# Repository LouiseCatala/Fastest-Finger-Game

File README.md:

<div align="center">

**KICAD · PCB LAYOUT · PRELIMINARY SCHEMATIC**

# FASTEST FINGER

### A three-player game concept, explored through PCB design.

[Explore the project](#project-overview) · [Documentation](#project-documentation) · [Contact the developer](mailto:louise.catala24@gmail.com)

</div>

<p align="center"><em>Existing KiCad 3D visualization. Component models are approximate; this is not a photograph of a fabricated board.</em></p>

## Project overview

An editable PCB-layout study for a three-player Fastest Finger game concept. The board brings player controls, a display, and supporting components into one visual design that can be explored in KiCad.

| At a glance | What it means |
| --- | --- |
| **3 players** | Three-player control layout |
| **KiCad project** | Editable board and schematic files |
| **174 × 128 mm** | Documented nominal board dimensions |

## Explore the design, with its status in view

**Design status: preliminary, not manufacturing-ready.** The layout was reconstructed from a supplied reference image. Traces are not fully routed, electrical connections and component choices need verification, and FPGA code is not included. The value here is an inspectable layout and schematic study, with its limitations stated openly.

*Preliminary schematic preview; retain the verification requirements in the original documentation below.*

[Explore the project package](Fastest-Finger-RevB)

## Project documentation

<details>
<summary><strong>Open the original project notes, files, and setup instructions</strong></summary>

# FASTEST FINGER — Made by Catala

This is an **editable KiCad PCB Editor board layout** recreated from the supplied reference image.

**Changes from the reference**
- All six names across the top have been removed.
- The bottom-center text now reads **Made by Catala**.
- The original title, three-player layout, approximate placement, and white decorative graphics are retained.

## PCB 3D Preview

The 3D visualization of the Fastest Finger PCB design created using KiCad.

## Schematic Diagram

The preliminary schematic diagram of the Fastest Finger circuit designed using KiCad Schematic Editor.

## Open in KiCad

1. Extract the whole ZIP; keep the `models` folder with the project files.
2. In KiCad Project Manager choose **File → Open Project** and select `Fastest_Finger_Made_by_Catala.kicad_pro`.
3. Double-click `Fastest_Finger_Made_by_Catala.kicad_pcb` from the project tree, or choose the PCB Editor shortcut.
4. In PCB Editor, use **View → 3D Viewer** (`Alt+3` on many systems) to see the approximate component models.
5. Edit text and locations directly on the **F.SilkS** and other PCB layers.
6. Open **Schematic Editor** to view or modify the `.kicad_sch` file.

Alternatively, start standalone PCB Editor and use **File → Open** to select the `.kicad_pcb` file. Do not try to select `.kicad_pcb` from KiCad Project Manager's **Open Project** file dialog, which filters for `.kicad_pro`.

## Hardware Components

| Component | Quantity |
|-----------|----------|
| Tang Nano 9K FPGA Board | 1 |
| 4-Digit 7-Segment Display | 1 |
| Player Push Buttons | 3 |
| START Button | 1 |
| RESET Button | 1 |
| NPN Transistors | 5 |
| Resistors | 17 |
| Capacitors | 2 |
| Diodes | 4 |
| LEDs | 2 |
| Buzzer | 1 |
| Mounting Holes | 4 |
| Printed Circuit Board | 1 |

## Important Limitation

This is a **visual/layout reconstruction with a preliminary schematic, not a verified, manufacturing-ready electronic design**.

The electrical connections, FPGA pin assignments, component values, and control wiring require verification. PCB traces are not fully routed, and FPGA code is not included.

Do not send the PCB for fabrication or assume functionality without verifying the actual circuit.

Real footprints and dimensions must be checked against the specific parts to be installed, especially the four-digit display, buttons, buzzer, and diodes. Visual models are approximations, not manufacturer STEP models.

- Board nominal dimensions: **174 mm × 128 mm**.
- Tang Nano 9K: represented by a **2 × 24 pin, 2.54 mm pitch** carrier footprint.
- Editable silkscreen labels and PCB features are part of the `.kicad_pcb` file.

---

**Made by Catala**

</details>

---

## License and Support

Copyright © 2026 Orland Louise Catala. All rights reserved for my original work, except where an existing license states otherwise. Third-party materials remain subject to their respective licenses.

Please do not copy, modify, redistribute, sell, or claim my original project files as your own without my permission.

I’m a student developer with limited financial resources, and these projects represent many hours of effort. Please respect and support my work. If you would like a copy of the project files, contact me at **[louise.catala24@gmail.com](mailto:louise.catala24@gmail.com)** to discuss a cheap price. Your support helps me continue studying and creating.

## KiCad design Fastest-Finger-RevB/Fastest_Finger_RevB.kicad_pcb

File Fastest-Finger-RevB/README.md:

# FASTEST FINGER — Made by Catala

This is an **editable KiCad PCB Editor board layout** recreated from the supplied reference image.

**Changes from the reference**
- All six names across the top have been removed.
- The bottom-center text now reads **Made by Catala**.
- The original title, three-player layout, approximate placement, and white decorative graphics are retained.

## PCB 3D Preview

The 3D visualization of the Fastest Finger PCB design created using KiCad.

## Schematic Diagram

The preliminary schematic diagram of the Fastest Finger circuit designed using KiCad Schematic Editor.

## Open in KiCad

1. Extract the whole ZIP; keep the `models` folder with the project files.
2. In KiCad Project Manager choose **File → Open Project** and select `Fastest_Finger_Made_by_Catala.kicad_pro`.
3. Double-click `Fastest_Finger_Made_by_Catala.kicad_pcb` from the project tree, or choose the PCB Editor shortcut.
4. In PCB Editor, use **View → 3D Viewer** (`Alt+3` on many systems) to see the approximate component models.
5. Edit text and locations directly on the **F.SilkS** and other PCB layers.
6. Open **Schematic Editor** to view or modify the `.kicad_sch` file.

Alternatively, start standalone PCB Editor and use **File → Open** to select the `.kicad_pcb` file. Do not try to select `.kicad_pcb` from KiCad Project Manager's **Open Project** file dialog, which filters for `.kicad_pro`.

## Hardware Components

| Component | Quantity |
|-----------|----------|
| Tang Nano 9K FPGA Board | 1 |
| 4-Digit 7-Segment Display | 1 |
| Player Push Buttons | 3 |
| START Button | 1 |
| RESET Button | 1 |
| NPN Transistors | 5 |
| Resistors | 17 |
| Capacitors | 2 |
| Diodes | 4 |
| LEDs | 2 |
| Buzzer | 1 |
| Mounting Holes | 4 |
| Printed Circuit Board | 1 |

## Important Limitation

This is a **visual/layout reconstruction with a preliminary schematic, not a verified, manufacturing-ready electronic design**.

The electrical connections, FPGA pin assignments, component values, and control wiring require verification. PCB traces are not fully routed, and FPGA code is not included.

Do not send the PCB for fabrication or assume functionality without verifying the actual circuit.

Real footprints and dimensions must be checked against the specific parts to be installed, especially the four-digit display, buttons, buzzer, and diodes. Visual models are approximations, not manufacturer STEP models.

- Board nominal dimensions: **174 mm × 128 mm**.
- Tang Nano 9K: represented by a **2 × 24 pin, 2.54 mm pitch** carrier footprint.
- Editable silkscreen labels and PCB features are part of the `.kicad_pcb` file.

---

**Made by Catala**

## License and Support

Copyright © 2026 Orland Louise Catala. All rights reserved for my original work, except where an existing license states otherwise. Third-party materials remain subject to their respective licenses.

Please do not copy, modify, redistribute, sell, or claim my original project files as your own without my permission.

I’m a student developer with limited financial resources, and these projects represent many hours of effort. Please respect and support my work. If you would like a copy of the project files, contact me at **[louise.catala24@gmail.com](mailto:louise.catala24@gmail.com)** to discuss a cheap price. Your support helps me continue studying and creating.

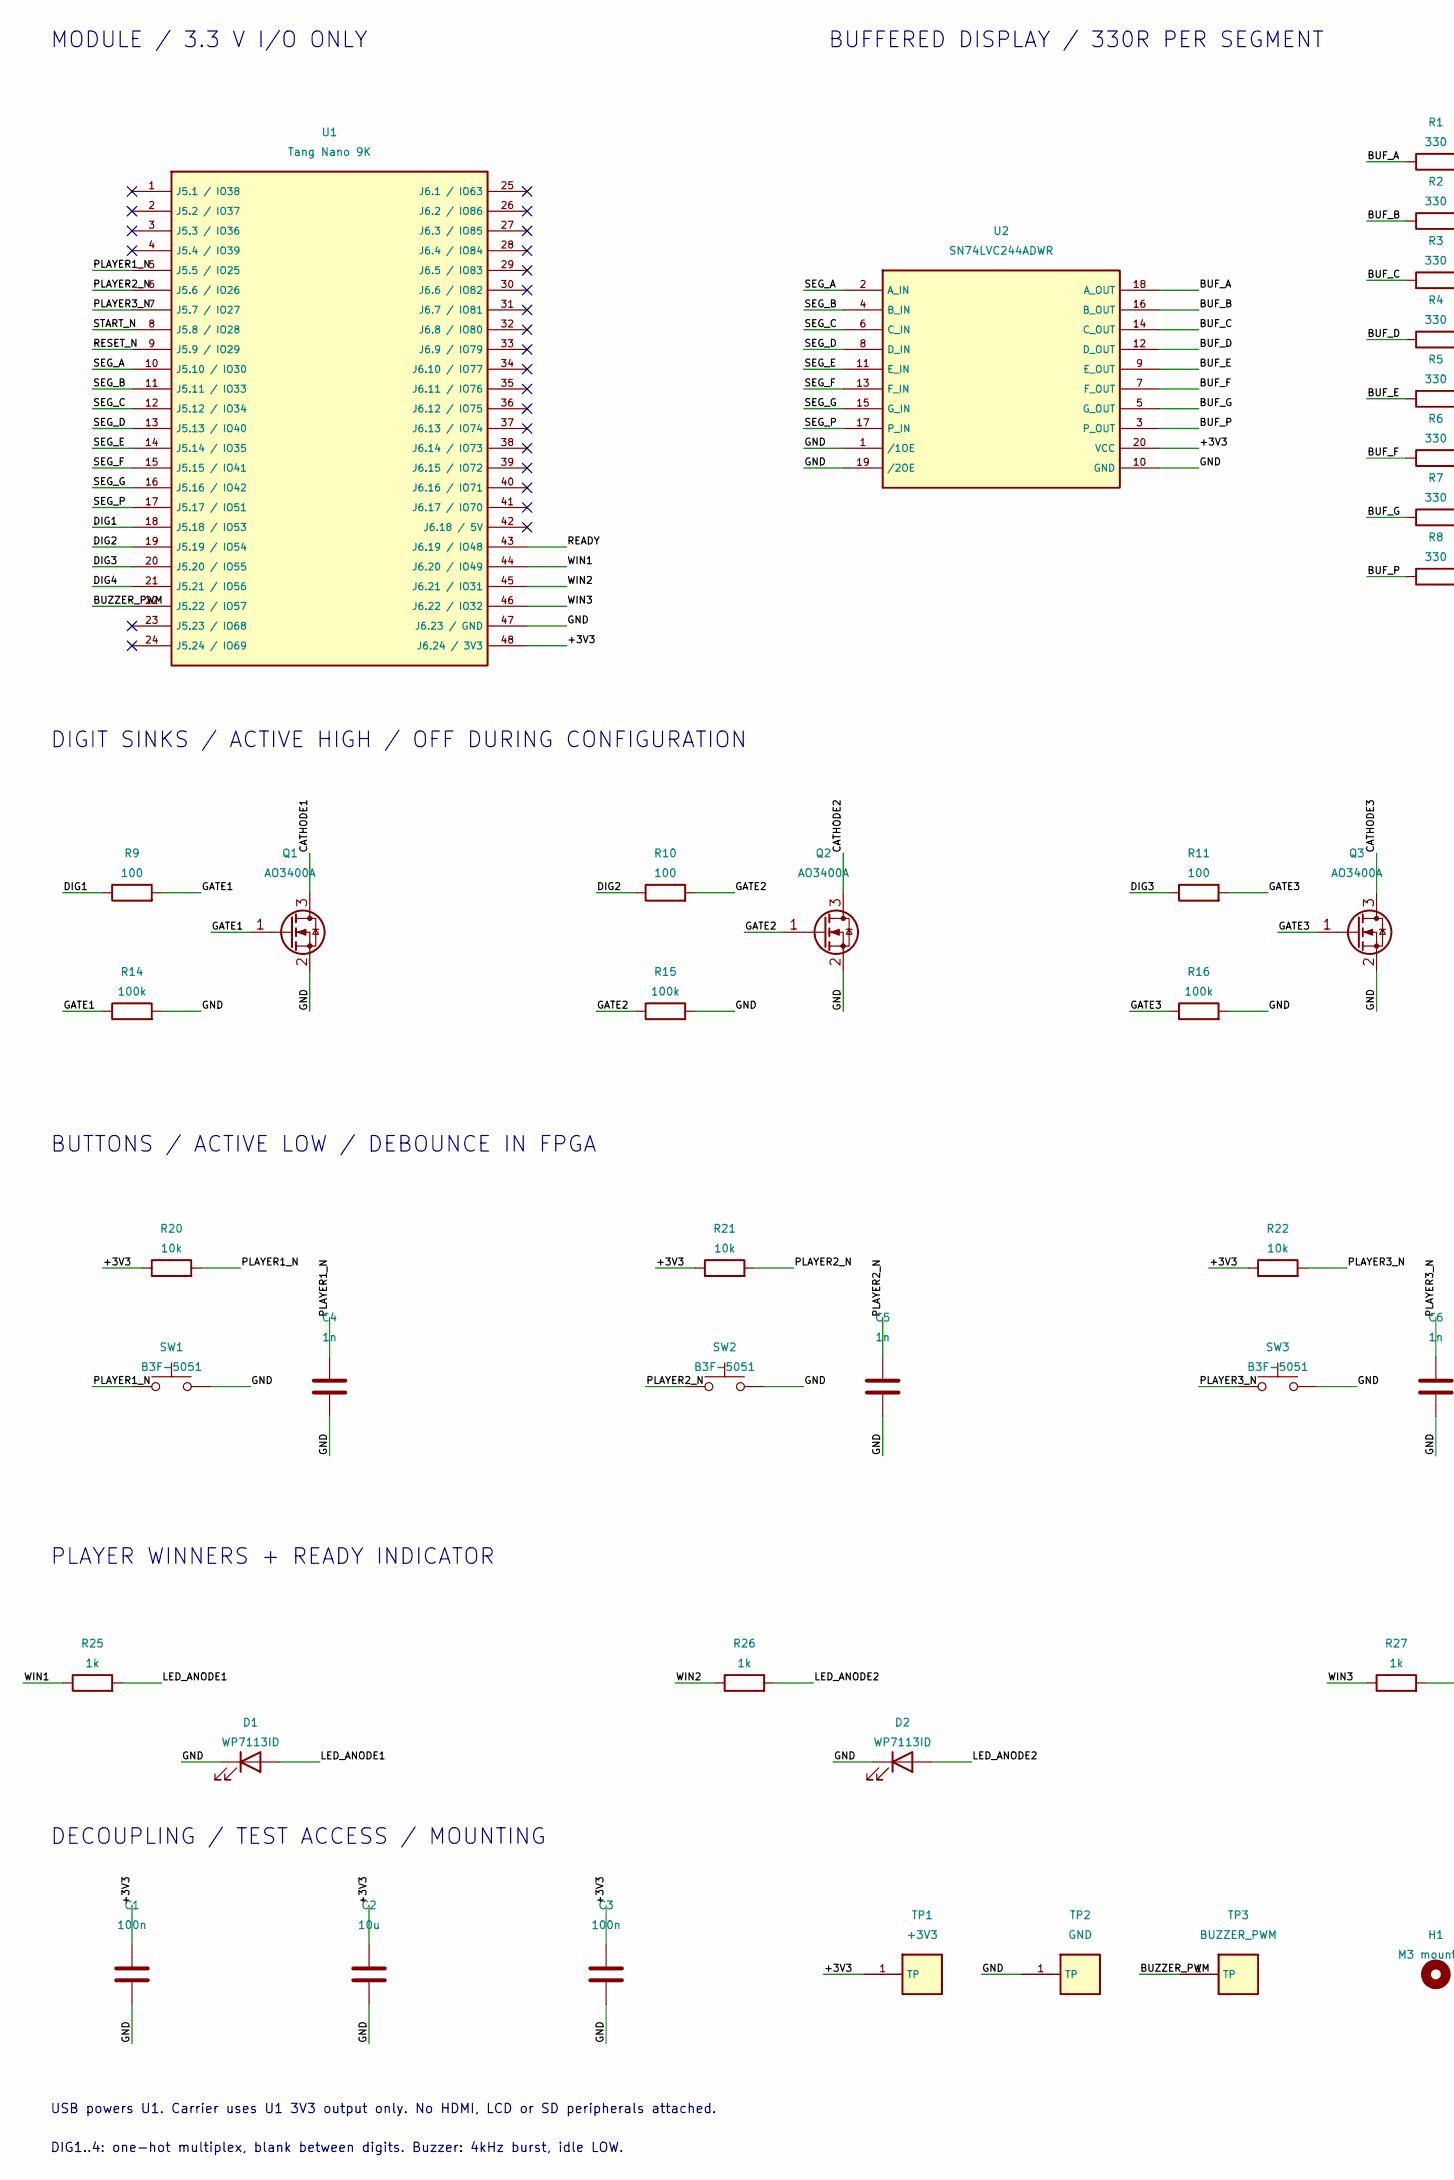
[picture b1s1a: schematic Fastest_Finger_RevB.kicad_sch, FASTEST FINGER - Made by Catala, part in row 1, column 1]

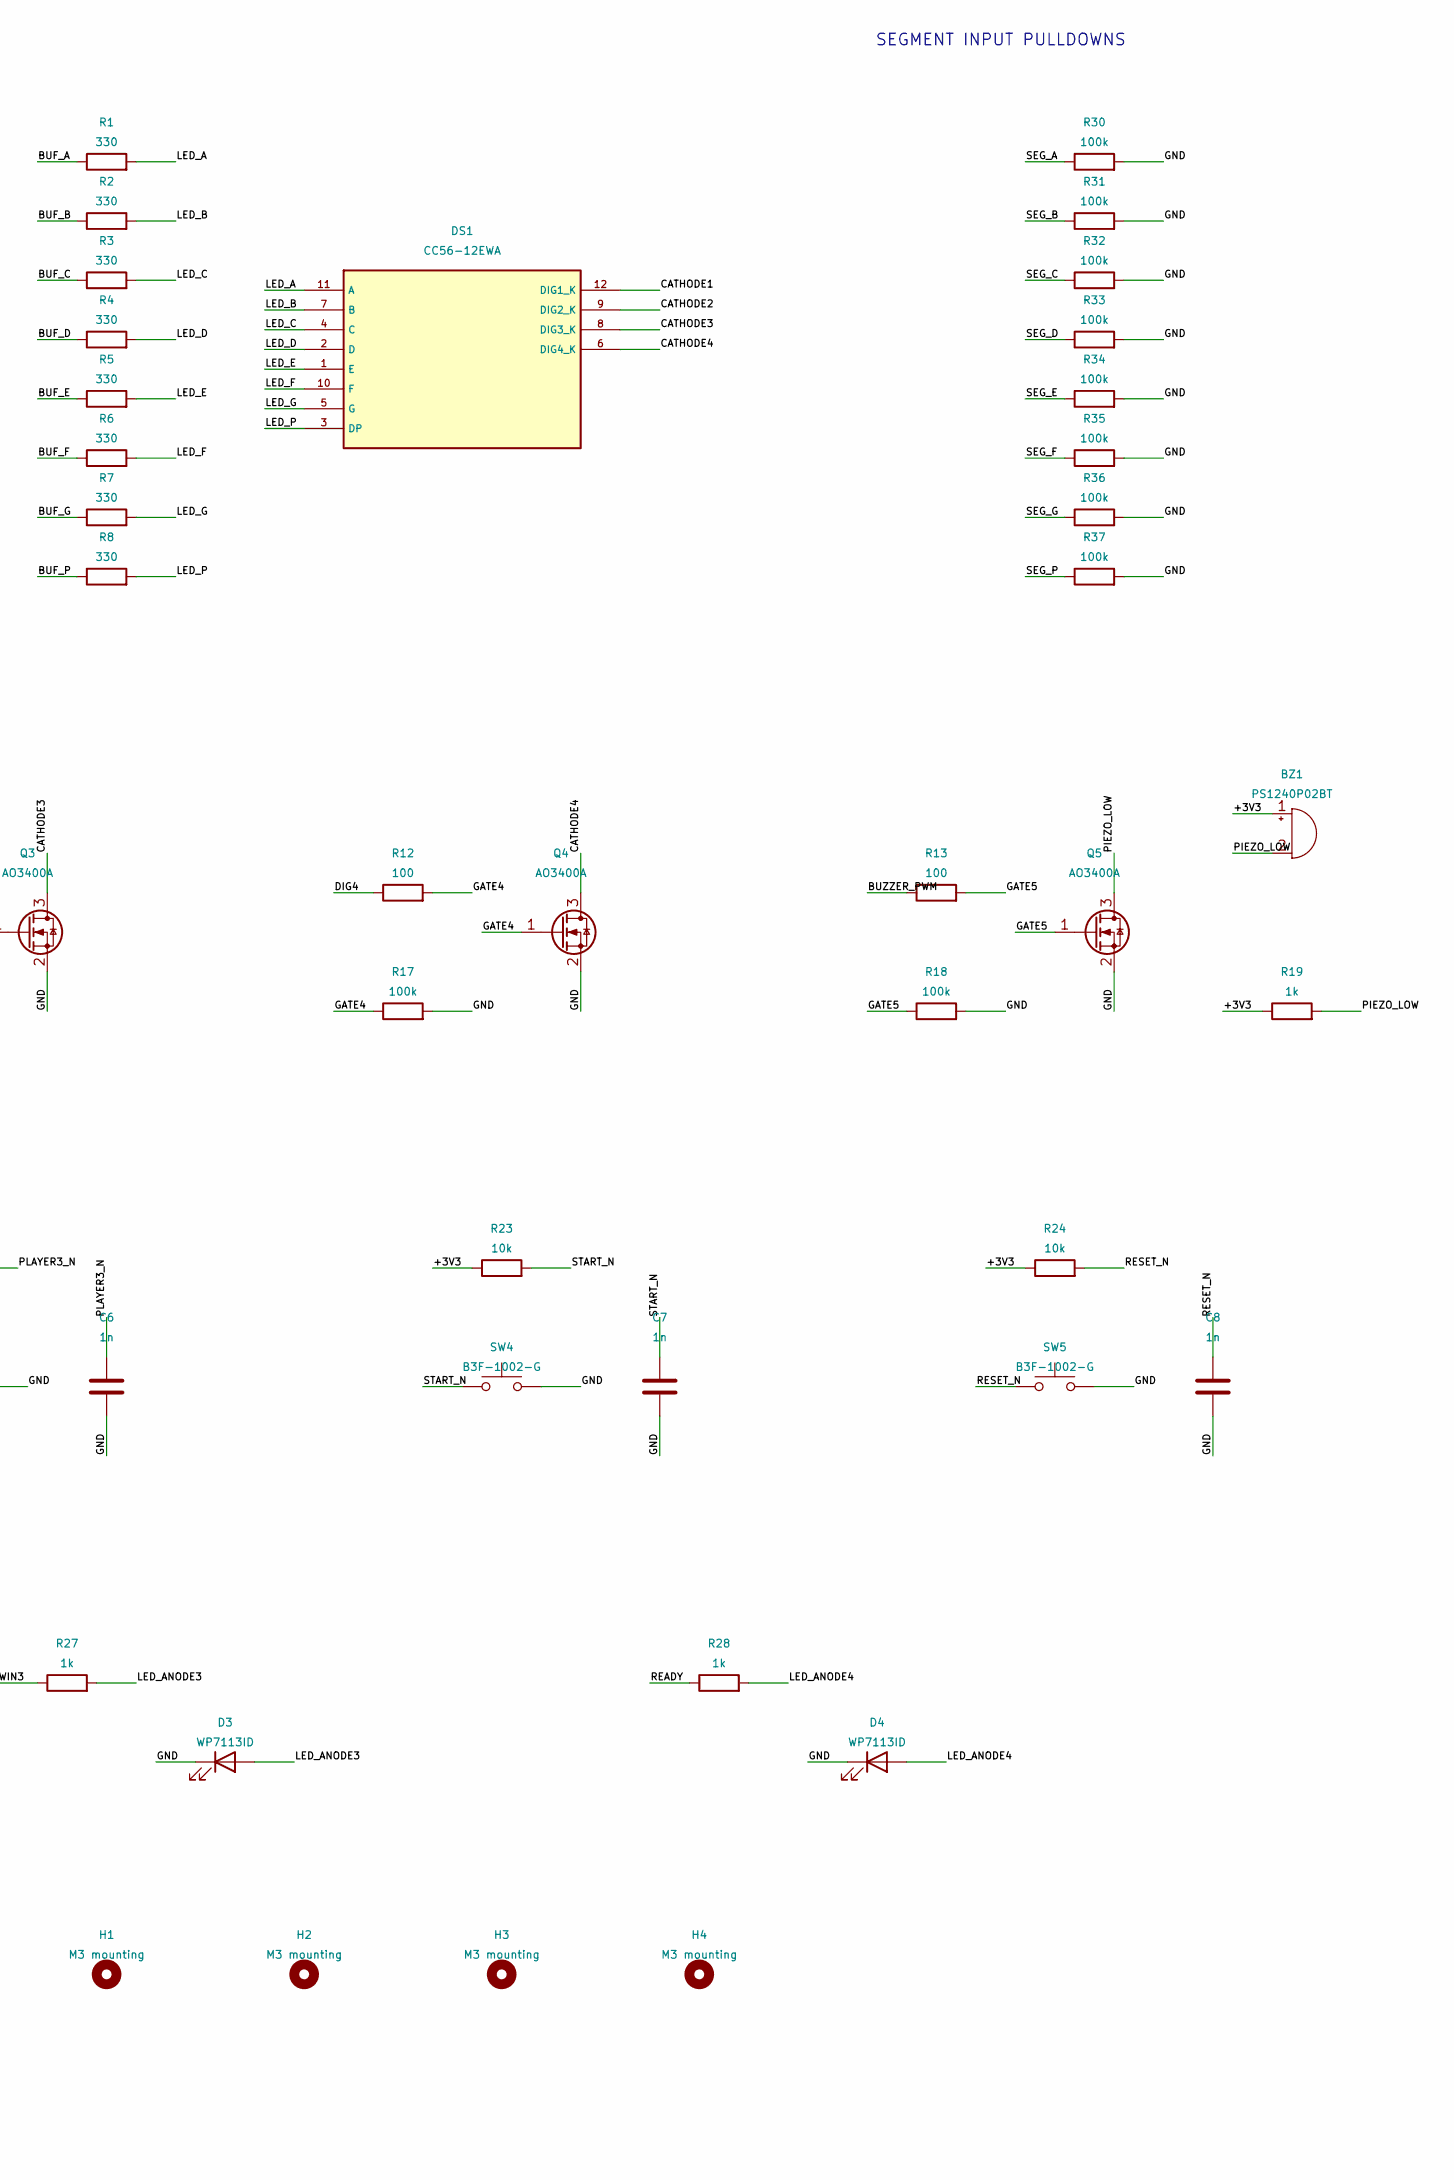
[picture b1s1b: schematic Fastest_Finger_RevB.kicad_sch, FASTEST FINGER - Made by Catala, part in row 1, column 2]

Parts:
BZ1: PS1240P02BT; Buzzer_TDK_PS1240P02BT_D12.2mm_H6.5mm; MPN PS1240P02BT
C1, C3: 100n; C_0805_2012Metric; MPN GRM21BR71H104KA01L
C2: 10u; C_0805_2012Metric; MPN GRM21BR61A106KE19L
C4, C5, C6, C7, C8: 1n; C_0805_2012Metric; MPN GRM21A5C1H102JA01D
D1, D2, D3, D4: WP7113ID; LED_D5.0mm; MPN WP7113ID
DS1: CC56-12EWA; CC56_12EWA; MPN CC56-12EWA
H1, H2, H3, H4: M3 mounting; MountingHole_3.2mm_M3; MPN M3 clearance hole
Q1, Q2, Q3, Q4, Q5: AO3400A; SOT-23; MPN AO3400A
R1, R2, R3, R4, R5, R6, R7, R8: 330; R_0805_2012Metric; MPN RC0805FR-07330RL
R9, R10, R11, R12, R13: 100; R_0805_2012Metric; MPN RC0805FR-07100RL
R14, R15, R16, R17, R18, R30, R31, R32, R33, R34, R35, R36, R37: 100k; R_0805_2012Metric; MPN RC0805FR-07100KL
R19, R25, R26, R27, R28: 1k; R_0805_2012Metric; MPN RC0805FR-071KL
R20, R21, R22, R23, R24: 10k; R_0805_2012Metric; MPN RC0805FR-0710KL
SW1, SW2, SW3: B3F-5051; SW_SPST_Omron_B3F-50xx; MPN B3F-5051
SW4, SW5: B3F-1002-G; SW_TH_Tactile_Omron_B3F-100x; MPN B3F-1002-G
TP1: +3V3; TestPoint_Pad_D2.0mm; MPN D2.0mm test pad
TP2: GND; TestPoint_Pad_D2.0mm; MPN D2.0mm test pad
TP3: BUZZER_PWM; TestPoint_Pad_D2.0mm; MPN D2.0mm test pad
U1: Tang Nano 9K; Tang_Nano_9K; MPN Tang Nano 9K
U2: SN74LVC244ADWR; SOIC-20W_7.5x12.8mm_P1.27mm; MPN SN74LVC244ADWR

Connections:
+3V3: BZ1.1 (+), C1.1, C2.1, C3.1, R19.1, R20.1, R21.1, R22.1, R23.1, R24.1, TP1.1, U1.48 (J6.24 / 3V3), U2.20 (VCC)
BUF_A: R1.1, U2.18 (A_OUT)
BUF_B: R2.1, U2.16 (B_OUT)
BUF_C: R3.1, U2.14 (C_OUT)
BUF_D: R4.1, U2.12 (D_OUT)
BUF_E: R5.1, U2.9 (E_OUT)
BUF_F: R6.1, U2.7 (F_OUT)
BUF_G: R7.1, U2.5 (G_OUT)
BUF_P: R8.1, U2.3 (P_OUT)
BUZZER_PWM: R13.1, TP3.1, U1.22 (J5.22 / IO57)
CATHODE1: DS1.12 (DIG1_K), Q1.3 (D)
CATHODE2: DS1.9 (DIG2_K), Q2.3 (D)
CATHODE3: DS1.8 (DIG3_K), Q3.3 (D)
CATHODE4: DS1.6 (DIG4_K), Q4.3 (D)
DIG1: R9.1, U1.18 (J5.18 / IO53)
DIG2: R10.1, U1.19 (J5.19 / IO54)
DIG3: R11.1, U1.20 (J5.20 / IO55)
DIG4: R12.1, U1.21 (J5.21 / IO56)
GATE1: Q1.1 (G), R9.2, R14.1
GATE2: Q2.1 (G), R10.2, R15.1
GATE3: Q3.1 (G), R11.2, R16.1
GATE4: Q4.1 (G), R12.2, R17.1
GATE5: Q5.1 (G), R13.2, R18.1
GND: C1.2, C2.2, C3.2, C4.2, C5.2, C6.2, C7.2, C8.2, D1.1 (K), D2.1 (K), D3.1 (K), D4.1 (K), Q1.2 (S), Q2.2 (S), Q3.2 (S), Q4.2 (S), Q5.2 (S), R14.2, R15.2, R16.2, R17.2, R18.2, R30.2, R31.2, R32.2, R33.2, R34.2, R35.2, R36.2, R37.2, SW1.2, SW2.2, SW3.2, SW4.2, SW5.2, TP2.1, U1.47 (J6.23 / GND), U2.1 (/1OE), U2.10 (GND), U2.19 (/2OE)
LED_A: DS1.11 (A), R1.2
LED_ANODE1: D1.2 (A), R25.2
LED_ANODE2: D2.2 (A), R26.2
LED_ANODE3: D3.2 (A), R27.2
LED_ANODE4: D4.2 (A), R28.2
LED_B: DS1.7 (B), R2.2
LED_C: DS1.4 (C), R3.2
LED_D: DS1.2 (D), R4.2
LED_E: DS1.1 (E), R5.2
LED_F: DS1.10 (F), R6.2
LED_G: DS1.5 (G), R7.2
LED_P: DS1.3 (DP), R8.2
PIEZO_LOW: BZ1.2 (-), Q5.3 (D), R19.2
PLAYER1_N: C4.1, R20.2, SW1.1, U1.5 (J5.5 / IO25)
PLAYER2_N: C5.1, R21.2, SW2.1, U1.6 (J5.6 / IO26)
PLAYER3_N: C6.1, R22.2, SW3.1, U1.7 (J5.7 / IO27)
READY: R28.1, U1.43 (J6.19 / IO48)
RESET_N: C8.1, R24.2, SW5.1, U1.9 (J5.9 / IO29)
SEG_A: R30.1, U1.10 (J5.10 / IO30), U2.2 (A_IN)
SEG_B: R31.1, U1.11 (J5.11 / IO33), U2.4 (B_IN)
SEG_C: R32.1, U1.12 (J5.12 / IO34), U2.6 (C_IN)
SEG_D: R33.1, U1.13 (J5.13 / IO40), U2.8 (D_IN)
SEG_E: R34.1, U1.14 (J5.14 / IO35), U2.11 (E_IN)
SEG_F: R35.1, U1.15 (J5.15 / IO41), U2.13 (F_IN)
SEG_G: R36.1, U1.16 (J5.16 / IO42), U2.15 (G_IN)
SEG_P: R37.1, U1.17 (J5.17 / IO51), U2.17 (P_IN)
START_N: C7.1, R23.2, SW4.1, U1.8 (J5.8 / IO28)
WIN1: R25.1, U1.44 (J6.20 / IO49)
WIN2: R26.1, U1.45 (J6.21 / IO31)
WIN3: R27.1, U1.46 (J6.22 / IO32)

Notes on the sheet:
MODULE / 3.3 V I/O ONLY
BUFFERED DISPLAY / 330R PER SEGMENT
SEGMENT INPUT PULLDOWNS
DIGIT SINKS / ACTIVE HIGH / OFF DURING CONFIGURATION
BUTTONS / ACTIVE LOW / DEBOUNCE IN FPGA
PLAYER WINNERS + READY INDICATOR
DECOUPLING / TEST ACCESS / MOUNTING
USB powers U1. Carrier uses U1 3V3 output only. No HDMI, LCD or SD peripherals attached.
DIG1..4: one-hot multiplex, blank between digits. Buzzer: 4kHz burst, idle LOW.

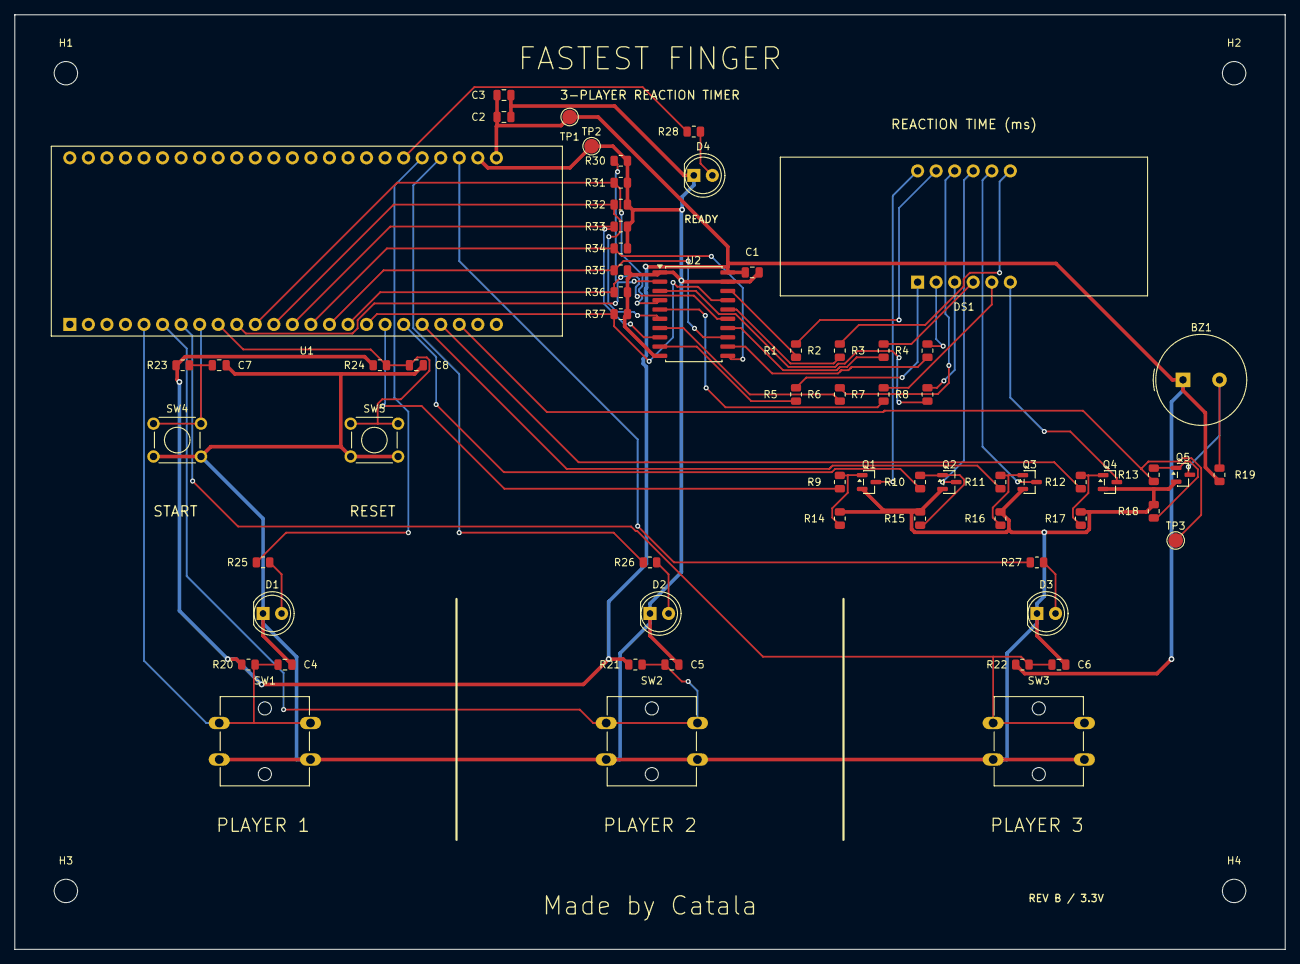
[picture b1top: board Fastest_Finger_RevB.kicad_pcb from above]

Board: 2 copper layers, 174.0 x 128.0 mm, 69 parts (0 on the bottom side), 54 nets.

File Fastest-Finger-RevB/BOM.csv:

Reference,Value,MPN,Manufacturer,Footprint,Datasheet
U1,Tang Nano 9K,Tang Nano 9K,Sipeed,FF_RevB:Tang_Nano_9K,https://dl.sipeed.com/fileList/TANG/Nano%209K/2_Schematic/Ta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
U2,SN74LVC244ADWR,SN74LVC244ADWR,Texas Instruments,FF_RevB:SOIC-20W_7.5x12.8mm_P1.27mm,https://www.ti.com/lit/ds/symlink/sn74lvc244a.pdf
DS1,CC56-12EWA,CC56-12EWA,Kingbright,FF_RevB:CC56_12EWA,https://www.kingbrightusa.com/images/catalog/SPEC/CC56-12EWA.pdf
R1,330,RC0805FR-07330RL,Yageo,FF_RevB:R_0805_2012Metric,
R30,100k,RC0805FR-07100KL,Yageo,FF_RevB:R_0805_2012Metric,
R2,330,RC0805FR-07330RL,Yageo,FF_RevB:R_0805_2012Metric,
R31,100k,RC0805FR-07100KL,Yageo,FF_RevB:R_0805_2012Metric,
R3,330,RC0805FR-07330RL,Yageo,FF_RevB:R_0805_2012Metric,
R32,100k,RC0805FR-07100KL,Yageo,FF_RevB:R_0805_2012Metric,
R4,330,RC0805FR-07330RL,Yageo,FF_RevB:R_0805_2012Metric,
R33,100k,RC0805FR-07100KL,Yageo,FF_RevB:R_0805_2012Metric,
R5,330,RC0805FR-07330RL,Yageo,FF_RevB:R_0805_2012Metric,
R34,100k,RC0805FR-07100KL,Yageo,FF_RevB:R_0805_2012Metric,
R6,330,RC0805FR-07330RL,Yageo,FF_RevB:R_0805_2012Metric,
R35,100k,RC0805FR-07100KL,Yageo,FF_RevB:R_0805_2012Metric,
R7,330,RC0805FR-07330RL,Yageo,FF_RevB:R_0805_2012Metric,
R36,100k,RC0805FR-07100KL,Yageo,FF_RevB:R_0805_2012Metric,
R8,330,RC0805FR-07330RL,Yageo,FF_RevB:R_0805_2012Metric,
R37,100k,RC0805FR-07100KL,Yageo,FF_RevB:R_0805_2012Metric,
Q1,AO3400A,AO3400A,Alpha & Omega,FF_RevB:SOT-23,https://www.aosmd.com/sites/default/files/res/datasheets/AO3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
R9,100,RC0805FR-07100RL,Yageo,FF_RevB:R_0805_2012Metric,
R14,100k,RC0805FR-07100KL,Yageo,FF_RevB:R_0805_2012Metric,
Q2,AO3400A,AO3400A,Alpha & Omega,FF_RevB:SOT-23,https://www.aosmd.com/sites/default/files/res/datasheets/AO3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
R10,100,RC0805FR-07100RL,Yageo,FF_RevB:R_0805_2012Metric,
R15,100k,RC0805FR-07100KL,Yageo,FF_RevB:R_0805_2012Metric,
Q3,AO3400A,AO3400A,Alpha & Omega,FF_RevB:SOT-23,https://www.aosmd.com/sites/default/files/res/datasheets/AO3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
R11,100,RC0805FR-07100RL,Yageo,FF_RevB:R_0805_2012Metric,
R16,100k,RC0805FR-07100KL,Yageo,FF_RevB:R_0805_2012Metric,
Q4,AO3400A,AO3400A,Alpha & Omega,FF_RevB:SOT-23,https://www.aosmd.com/sites/default/files/res/datasheets/AO3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
R12,100,RC0805FR-07100RL,Yageo,FF_RevB:R_0805_2012Metric,
R17,100k,RC0805FR-07100KL,Yageo,FF_RevB:R_0805_2012Metric,
Q5,AO3400A,AO3400A,Alpha & Omega,FF_RevB:SOT-23,https://www.aosmd.com/sites/default/files/res/datasheets/AO3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
R13,100,RC0805FR-07100RL,Yageo,FF_RevB:R_0805_2012Metric,
R18,100k,RC0805FR-07100KL,Yageo,FF_RevB:R_0805_2012Metric,
BZ1,PS1240P02BT,PS1240P02BT,TDK,FF_RevB:Buzzer_TDK_PS1240P02BT_D12.2mm_H6.5mm,https://product.tdk.com/system/files/dam/doc/product/sw_piez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
R19,1k,RC0805FR-071KL,Yageo,FF_RevB:R_0805_2012Metric,
SW1,B3F-5051,B3F-5051,Omron,FF_RevB:SW_SPST_Omron_B3F-50xx,https://components.omron.com/us-en/datasheet_pdf/A070-E1.pdf
R20,10k,RC0805FR-0710KL,Yageo,FF_RevB:R_0805_2012Metric,
C4,1n,GRM21A5C1H102JA01D,Murata,FF_RevB:C_0805_2012Metric,
SW2,B3F-5051,B3F-5051,Omron,FF_RevB:SW_SPST_Omron_B3F-50xx,https://components.omron.com/us-en/datasheet_pdf/A070-E1.pdf
R21,10k,RC0805FR-0710KL,Yageo,FF_RevB:R_0805_2012Metric,
C5,1n,GRM21A5C1H102JA01D,Murata,FF_RevB:C_0805_2012Metric,
SW3,B3F-5051,B3F-5051,Omron,FF_RevB:SW_SPST_Omron_B3F-50xx,https://components.omron.com/us-en/datasheet_pdf/A070-E1.pdf
R22,10k,RC0805FR-0710KL,Yageo,FF_RevB:R_0805_2012Metric,
C6,1n,GRM21A5C1H102JA01D,Murata,FF_RevB:C_0805_2012Metric,
SW4,B3F-1002-G,B3F-1002-G,Omron,FF_RevB:SW_TH_Tactile_Omron_B3F-100x,https://components.omron.com/us-en/datasheet_pdf/A070-E1.pdf
R23,10k,RC0805FR-0710KL,Yageo,FF_RevB:R_0805_2012Metric,
C7,1n,GRM21A5C1H102JA01D,Murata,FF_RevB:C_0805_2012Metric,
SW5,B3F-1002-G,B3F-1002-G,Omron,FF_RevB:SW_TH_Tactile_Omron_B3F-100x,https://components.omron.com/us-en/datasheet_pdf/A070-E1.pdf
R24,10k,RC0805FR-0710KL,Yageo,FF_RevB:R_0805_2012Metric,
C8,1n,GRM21A5C1H102JA01D,Murata,FF_RevB:C_0805_2012Metric,
D1,WP7113ID,WP7113ID,Kingbright,FF_RevB:LED_D5.0mm,https://www.kingbrightusa.com/images/catalog/SPEC/WP7113ID.pdf
R25,1k,RC0805FR-071KL,Yageo,FF_RevB:R_0805_2012Metric,
D2,WP7113ID,WP7113ID,Kingbright,FF_RevB:LED_D5.0mm,https://www.kingbrightusa.com/images/catalog/SPEC/WP7113ID.pdf
R26,1k,RC0805FR-071KL,Yageo,FF_RevB:R_0805_2012Metric,
D3,WP7113ID,WP7113ID,Kingbright,FF_RevB:LED_D5.0mm,https://www.kingbrightusa.com/images/catalog/SPEC/WP7113ID.pdf
R27,1k,RC0805FR-071KL,Yageo,FF_RevB:R_0805_2012Metric,
D4,WP7113ID,WP7113ID,Kingbright,FF_RevB:LED_D5.0mm,https://www.kingbrightusa.com/images/catalog/SPEC/WP7113ID.pdf
R28,1k,RC0805FR-071KL,Yageo,FF_RevB:R_0805_2012Metric,
C1,100n,GRM21BR71H104KA01L,Murata,FF_RevB:C_0805_2012Metric,
C2,10u,GRM21BR61A106KE19L,Murata,FF_RevB:C_0805_2012Metric,
C3,100n,GRM21BR71H104KA01L,Murata,FF_RevB:C_0805_2012Metric,
H1,M3 mounting,M3 clearance hole,Mechanical,FF_RevB:MountingHole_3.2mm_M3,
H2,M3 mounting,M3 clearance hole,Mechanical,FF_RevB:MountingHole_3.2mm_M3,
H3,M3 mounting,M3 clearance hole,Mechanical,FF_RevB:MountingHole_3.2mm_M3,
H4,M3 mounting,M3 clearance hole,Mechanical,FF_RevB:MountingHole_3.2mm_M3,
TP1,+3V3,D2.0mm test pad,PCB,FF_RevB:TestPoint_Pad_D2.0mm,
TP2,GND,D2.0mm test pad,PCB,FF_RevB:TestPoint_Pad_D2.0mm,
TP3,BUZZER_PWM,D2.0mm test pad,PCB,FF_RevB:TestPoint_Pad_D2.0mm,

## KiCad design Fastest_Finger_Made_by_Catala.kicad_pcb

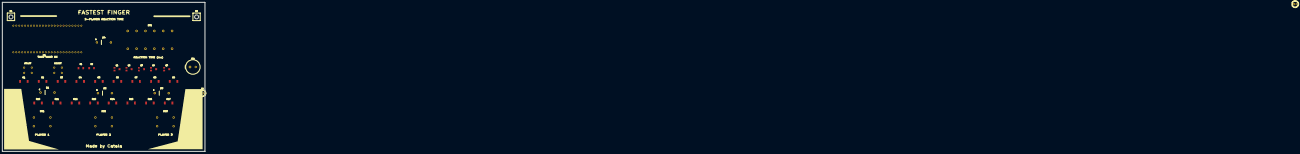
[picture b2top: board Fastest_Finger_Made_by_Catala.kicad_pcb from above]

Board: 2 copper layers, 174.0 x 128.0 mm, 42 parts (0 on the bottom side), 38 nets, no tracks yet.

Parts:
BZ1: Buzzer_TDK_PS1240P02BT_D12.2mm_H6.5mm
C1, C2: Capacitor; Cap_1206
D1, D2, D3, D4: Diode; Diode_DO41_P7.62
D5, D6: LED_D5.0mm
DS1: 4-digit display; Display_4Digit_7Segment_54x21
H1, H2, H3, H4: Mounting Hole; MountingHole_3.4mm
Q1, Q2, Q3, Q4, Q5: Transistor; SOT23_3Pin
R1, R2, R3, R4, R5, R6, R7, R8, R9, R10, R11, R12, R13, R14, R15, R16, R17: R; Resistor_2512
SW1, SW2, SW3: Pushbutton 12 mm; SW_Tact_12mm
SW4, SW5: Pushbutton 6 mm; SW_Tact_6mm
U1: Tang Nano 9K; Tang_Nano_9K_2x24

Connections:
+3V3: BZ1.1, C1.1, C2.1, R13.1, R14.1, R15.1, R16.1, U1.1
BTN_P1: R13.2, SW1.1, U1.3
BTN_P2: R14.2, SW2.1, U1.4
BTN_P3: R15.2, SW3.1, U1.5
BTN_RESET: SW5.1, U1.7
BTN_START: R16.2, SW4.1, U1.6
BUZZ_BASE: Q5.1, R17.2
BUZZ_GPIO: R17.1, U1.20
BUZZ_NEG: BZ1.2, Q5.3
DIG1: DS1.12, Q1.3
DIG1_BASE: Q1.1, R9.2
DIG1_GPIO: R9.1, U1.16
DIG2: DS1.9, Q2.3
DIG2_BASE: Q2.1, R10.2
DIG2_GPIO: R10.1, U1.17
DIG3: DS1.8, Q3.3
DIG3_BASE: Q3.1, R11.2
DIG3_GPIO: R11.1, U1.18
DIG4: DS1.6, Q4.3
DIG4_BASE: Q4.1, R12.2
DIG4_GPIO: R12.1, U1.19
GND: C1.2, C2.2, Q1.2, Q2.2, Q3.2, Q4.2, Q5.2, SW1.2, SW2.2, SW3.2, SW4.2, SW5.2, U1.2
SEG_A: DS1.11, R1.2
SEG_A_GPIO: R1.1, U1.8
SEG_B: DS1.7, R2.2
SEG_B_GPIO: R2.1, U1.9
SEG_C: DS1.4, R3.2
SEG_C_GPIO: R3.1, U1.10
SEG_D: DS1.2, R4.2
SEG_DP: DS1.3, R8.2
SEG_DP_GPIO: R8.1, U1.15
SEG_D_GPIO: R4.1, U1.11
SEG_E: DS1.1, R5.2
SEG_E_GPIO: R5.1, U1.12
SEG_F: DS1.10, R6.2
SEG_F_GPIO: R6.1, U1.13
SEG_G: DS1.5, R7.2
SEG_G_GPIO: R7.1, U1.14
